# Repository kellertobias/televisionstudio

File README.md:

# Tobisk Television Studio Control Panel (ToskTVStudio)

This Project contains all software and hardware sources necessary to control a setup consisting of:

- ATEM Television Studio HD Video Switcher
- Web Presenter/ Hyperdeck (Work in Progress)
- OBS for graphics optionally streaming/recording
- Website based text generator for OBS
- MOTU828es based Audio Mixing (Work in Progress)
- LoRa Based Camera Tallys and Python based Tally base

The main part of this project is a nodejs based application that provides the control of the infrastructure via macros and all required additional services.

This System contains of these services:
- Main Control Desk Software
- Server to send Tally Signals (might run on the same raspberry pi as the control desk)
- Server to communicate with the hardware of the control desk
- Web based Textgenerator for OBS (or any other web browser)

as well as the firmware and schematics for these hardware components:
- LoRa Based Tally Sender and Receiver
- Desk Hardware Buttons, faders and encoders

## Control desk Software

The main part of this software is the control desk software which is capable of controlling ATEM switchers and OBS (Hyperdeck and Web Presenter Support is work in progress). This software is meant to run on a raspberry PI and provides the user interface via a website. there is also a serial interface to an arduino based keyboard interface (split up in a separate server for easier developing).

## Control desk Hardware

The main part of this software is the control desk software which is capable of controlling ATEM switchers and OBS (Hyperdeck and Web Presenter Support is work in progress). This software is meant to run on a raspberry PI and provides the user interface via a website. there is also a serial interface to an arduino based keyboard interface (split up in a separate server for easier developing).

## Tally System

The tally system is based on LoRa communications.
There is a server that is meant to run on the same raspberry pi as the control desk software. The control desk software sends to the LoRa server which channel is on program and which is on preview. This happens over a simple REST api.
However if you want to use the tally system without the control desk software, you can do so, but need to write this part your own. there are multiple libraries providing this.

The tally system consists out of:

- Tally Server: `/services/tally-lora-server`
- Tally Client Firmware & Hardware: `/services/tally-lora-client`

More information on this is in the README.md of that subproject: 

## Text-Generator

The last part of this software is a textgenerator. It is meant to be embedded as a webpage in OBS or as Fullscreen Browser Screen on a second raspberry pi and connected to the ATEM.

The textgenerator supports countdowns, scrolling texts and lower thirds

# Development and Operations

The software is written in Typescript and requires `node` and `npm` to be installed. You can then use `npm`'s scripts to execute development scripts.  

-   `npm i -D` for installing all the dependencies
-   `npm run dev` - Start Development Environment. Client and server are in watch mode with source maps, opens [http://localhost:3000](http://localhost:3000)

### Deploying

-   `npm run build` - `dist` folder will include all the needed files, both client (Bundle) and server.
-   `npm start` - Just runs `node ./dist/server/server.js`
-   `npm start:prod` - sets `NODE_ENV` to `production` and then runs `node ./dist/server/server.js`. (Bypassing webpack proxy)

### Technology Stack

Backend:

- `node.js` as runtime
- `typescript` as programming language
- `express` for APIs

Frontend:

- `webpack 5` for bundling
- `react` as UI Framework
- `storybook` for developing components
- `axios` for contacting the REST APIs

# Todo-List/ Roadmap

- [ ] get rid of meteor and move to a more modern build stack
- [ ] rewrite Web UI to be Typescript
- [ ] re-send tally commands multiple times
- [ ] Add Web Presenter Support (Start/Stop Stream, Show Stream Status, Set Stream Target configured in the showfile)
- [ ] Add Support for Audio Level Monitoring and Audio Control
- [ ] Add a second web interface for configuring the software, e.g. over an iPad or Laptop
- [ ] allow in-software macro editing and showfile configuration

# License

This software might only be used for non-commercial purposes, this means, you may not sell it or anything that builds upon it. You may however use your own products based on this software for commercial purposes.

Permission is hereby granted, free of charge, to any person obtaining a copy of this software and associated documentation files (the "Software"), to deal in the Software with the abovegiven restrictions, including with the abovegiven limitations the rights to use, copy, modify, merge, publish, distribute, of the Software, and to permit persons to whom the Software is furnished to do so, subject to the following conditions:

The above copyright notice and this permission notice shall be included in all copies or substantial portions of the Software.

THE SOFTWARE IS PROVIDED "AS IS", WITHOUT WARRANTY OF ANY KIND, EXPRESS OR IMPLIED, INCLUDING BUT NOT LIMITED TO THE WARRANTIES OF MERCHANTABILITY, FITNESS FOR A PARTICULAR PURPOSE AND NONINFRINGEMENT. IN NO EVENT SHALL THE AUTHORS OR COPYRIGHT HOLDERS BE LIABLE FOR ANY CLAIM, DAMAGES OR OTHER LIABILITY, WHETHER IN AN ACTION OF CONTRACT, TORT OR OTHERWISE, ARISING FROM, OUT OF OR IN CONNECTION WITH THE SOFTWARE OR THE USE OR OTHER DEALINGS IN THE SOFTWARE.

## References to packages and content this work is based on
- Boilerplate: https://github.com/gilamran/fullstack-typescript.git

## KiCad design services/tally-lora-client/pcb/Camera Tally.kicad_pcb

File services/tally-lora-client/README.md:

# Lora Tally Node

This part of the Project is a little Device (and the software for it), that you can stick onto the camera
and Lights up if the camera is on Program or Preview.

This part consists of the `lora-node.ino`, the arduino sourcecode for the Wemos D1, a little Python Script for the
Raspberry Pi to test the nodes and of the schematics and board layout.

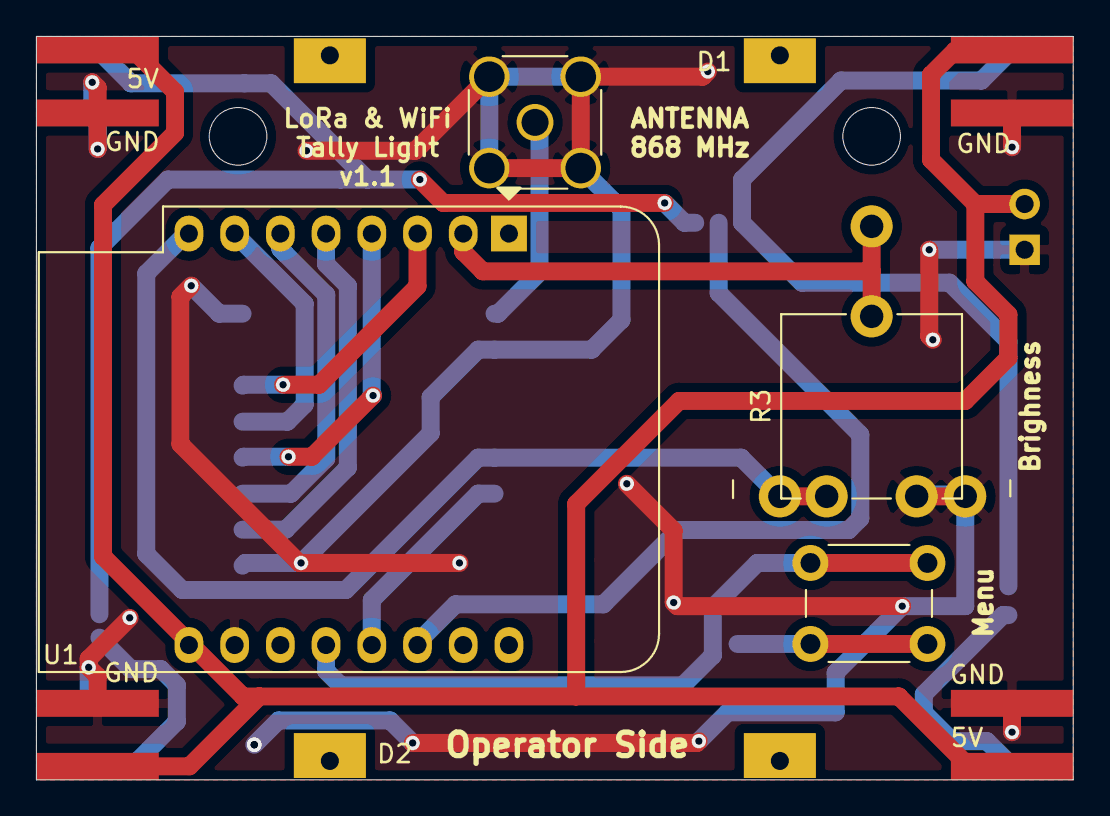
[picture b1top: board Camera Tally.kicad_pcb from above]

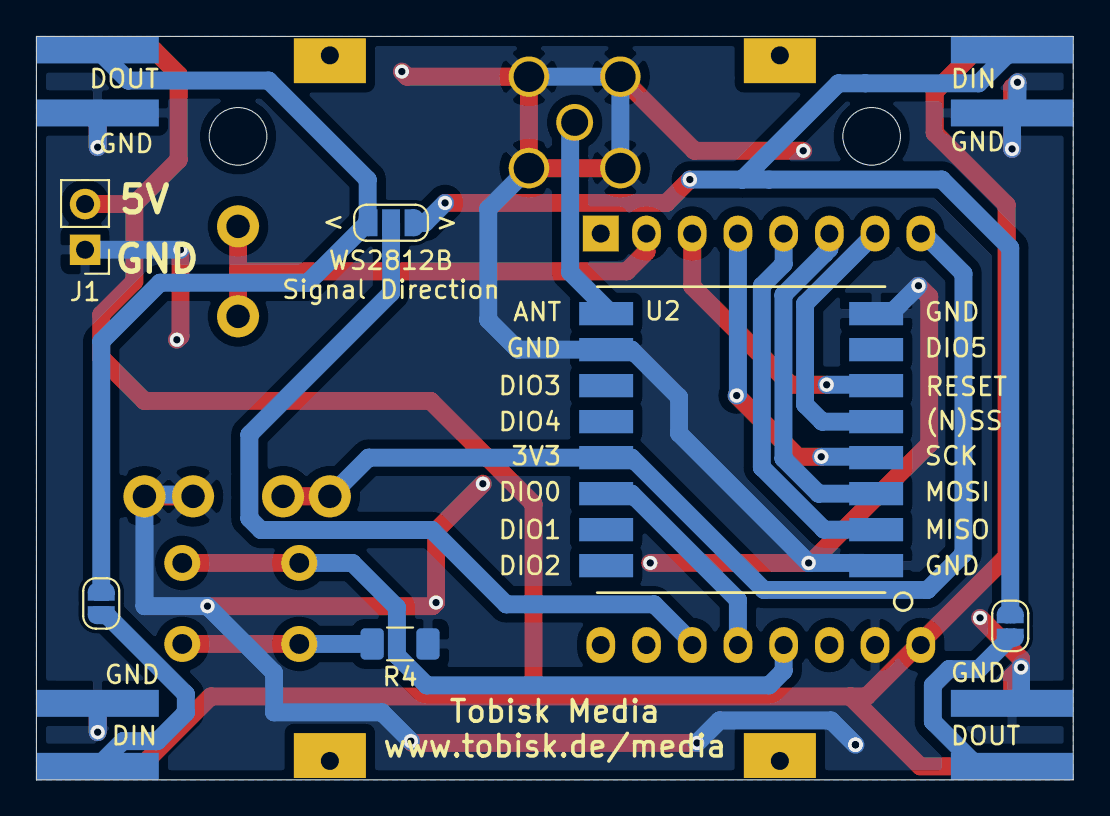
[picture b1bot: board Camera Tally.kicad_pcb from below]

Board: 2 copper layers, 57.6 x 41.3 mm, 14 parts (6 on the bottom side), 18 nets.

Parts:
AE2: Antenna_Shield; SMA_Wurth_60312002114503_Vertical
D1, D2: WS2812B; WS2812B_8x_5cm
H1, H2: MountingHole; MountingHole_3.2mm_M3
J1: Screw_Terminal_01x02; PinHeader_1x02_P2.54mm_Vertical
JP1, JP3: Jumper; SolderJumper-2_P1.3mm_Open_RoundedPad1.0x1.5mm
JP2: Jumper_NC_Dual; SolderJumper-3_P1.3mm_Open_RoundedPad1.0x1.5mm
R3: POT; Potentiometer_ACP_CA9-V10_Vertical
R4: R; R_1206_3216Metric_Pad1.30x1.75mm_HandSolder
SW1: SW_Push; SW_PUSH_6mm_H7.3mm
U1: WeMos_D1_mini; WEMOS_D1_mini_light
U2: RFM95W-868S2; RFM9X-SMD

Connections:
+3V3: R3.3, U1.8, U2.13
+5V: D1.1, D2.1, J1.2, U1.9
/ANT: AE2.1, U2.9
/MISO: U1.5, U2.2
/MOSI: U1.6, U2.3
/POT: R3.2, U1.2
/RFM_INT: U1.13, U2.14
/RFM_RES: U1.3, U2.6
/SCK: U1.4, U2.4
/SS: U1.7, U2.5
/SW1: SW1.1, U1.12
/WS2812B: JP2.2, U1.14
GND: AE2.2, D1.3, D2.3, J1.1, R3.1, R4.1, U1.10, U2.1, U2.8, U2.10
unnamed: D1.2, JP2.3, JP3.1
unnamed: D1.4, JP1.1, JP2.1
unnamed: D2.2, JP1.2
unnamed: D2.4, JP3.2
unnamed: R4.2, SW1.2

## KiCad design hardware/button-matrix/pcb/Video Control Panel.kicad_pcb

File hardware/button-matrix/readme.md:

# Control-Panel Button Matrix

The Control Panel consists of two Button Matrix Boards, connected via USB to a Raspberry PI as well as a Touchscreen and some miscalaneous electronics such as fans and a power supply.

The Button Matrix has at most 5 rows of 9 buttons each and can be cut so that it is 5x8. Each button has a WS2812b LED assigned to it.

The buttons and LEDs are numbered from the top left, row by row.

This means that the top left button has the number 11 (first row, first button), the last button of this row has the number 19.
The first button in the last row has the number 51, the last one 59. In the communication protocol, the ws2812b LEDs are also addressed by the button number.

The buttons might be populated or not, depending on the configuration required for the use case. If the button is not populated, the LED usually is also not populated, however the external addressing stays the same (meaning there is some calculation required.)

There are also some additional user inputs on the PCB, namely a push encoder and a linear slider.

The total addressing in the protocol is the following (the values are the range of values of the second byte, the value byte):

- 0 - System Messages (0 = startup, 255 = unit/connection will shutdown)
- 1 - LED Brightness Bright (0-255 for dark to bright)
- 2 - LED Brightness Dark (0-255 for dark to bright)
- 9 - Encoder Turn (1 = Left Turn, 2 = Right Turn, Encoder Push is the same contact as button 58)
- 10 - Linear Slider (0-255 for 0v to 5V)
- 11 - Row 1 Button/LED 1 (for button: 0 = not pressed, 1 = pressed, for LED: one byte containing two sets of colors)
- ...
- 19 - Row 1 Button/LED 9 (...)
- ...
- 59 - Row 5 Button/LED 9 (...)

# Communication Protocol

The Communication Protocol uses UART and the first Byte in a Message defines the entity as described above.
When the Device starts up, it sends a Zero-Byte. Messages where the first byte is zero are system messages.

## Event-Messages from PCB to Master (Buttons and Faders)

when sending input messages, such as button presses or fader value changes, the first byte is the address, the second one is the state, such as 0 or 1 for a button (0 = not pressed, 1 = pressed) or 0-255 for a fader (where the range of the fader is mapped to 0-255).

The Encoder, if populated also can send messages. If it turns left, the message is 1 (per click), for right it is 2.
The push of the encoder is the same as button number 58

## Event-Messages from Master to PCB (LED status change, Brightness)

The master might also send messages to the controller, containing LED states.
The value of the led states is as follows:

ON R | ON G | ON B | BLINK R | BLINK G | BLINK B | BLINK FAST=1/SLOW=0 | DIM BRIGHT=1/DARK=0

the led needs to change color 4 times a second, if blink=fast, two times a second if blink=slow. It changes from the color from he first three bits to the one of the last three bits.
The Color is always mapped from bit to byte => 0 = 0x00 and 1 = 0x01 \* global brightness

Thus the brightness is determined by the globally set brightess, which is set by a message on address 1 (or 2 if the last bit of the led value is set to 0 and thus its meant to be a dark glow)

# Connections

For the connection diagram see

Note that the Diodes are Placed in reverse order to the Circuit.
So the Rows are the Output, which are set to high and the columns are the inputs, which can be read (High = Pressed, Low = Open)

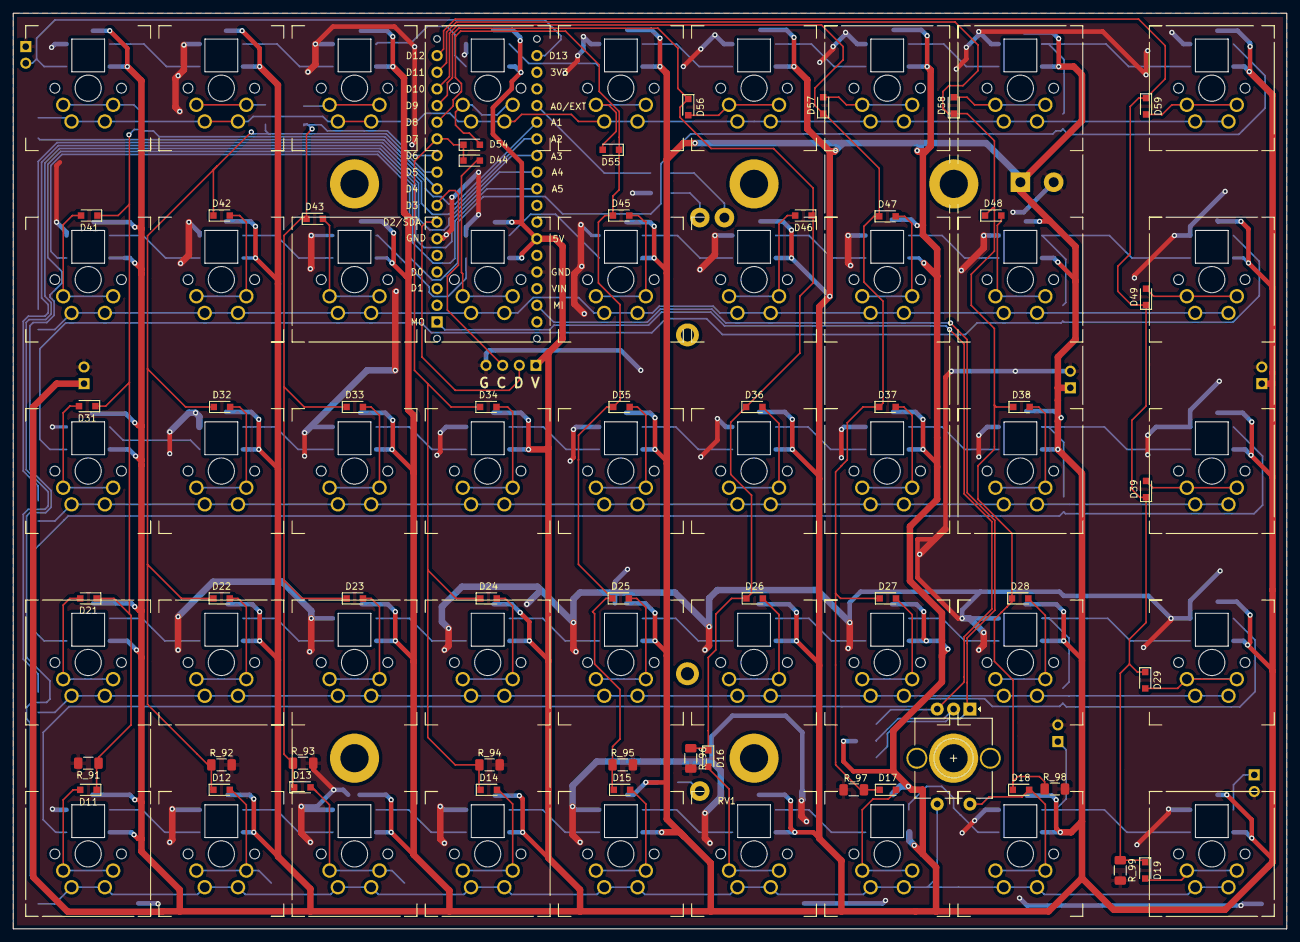
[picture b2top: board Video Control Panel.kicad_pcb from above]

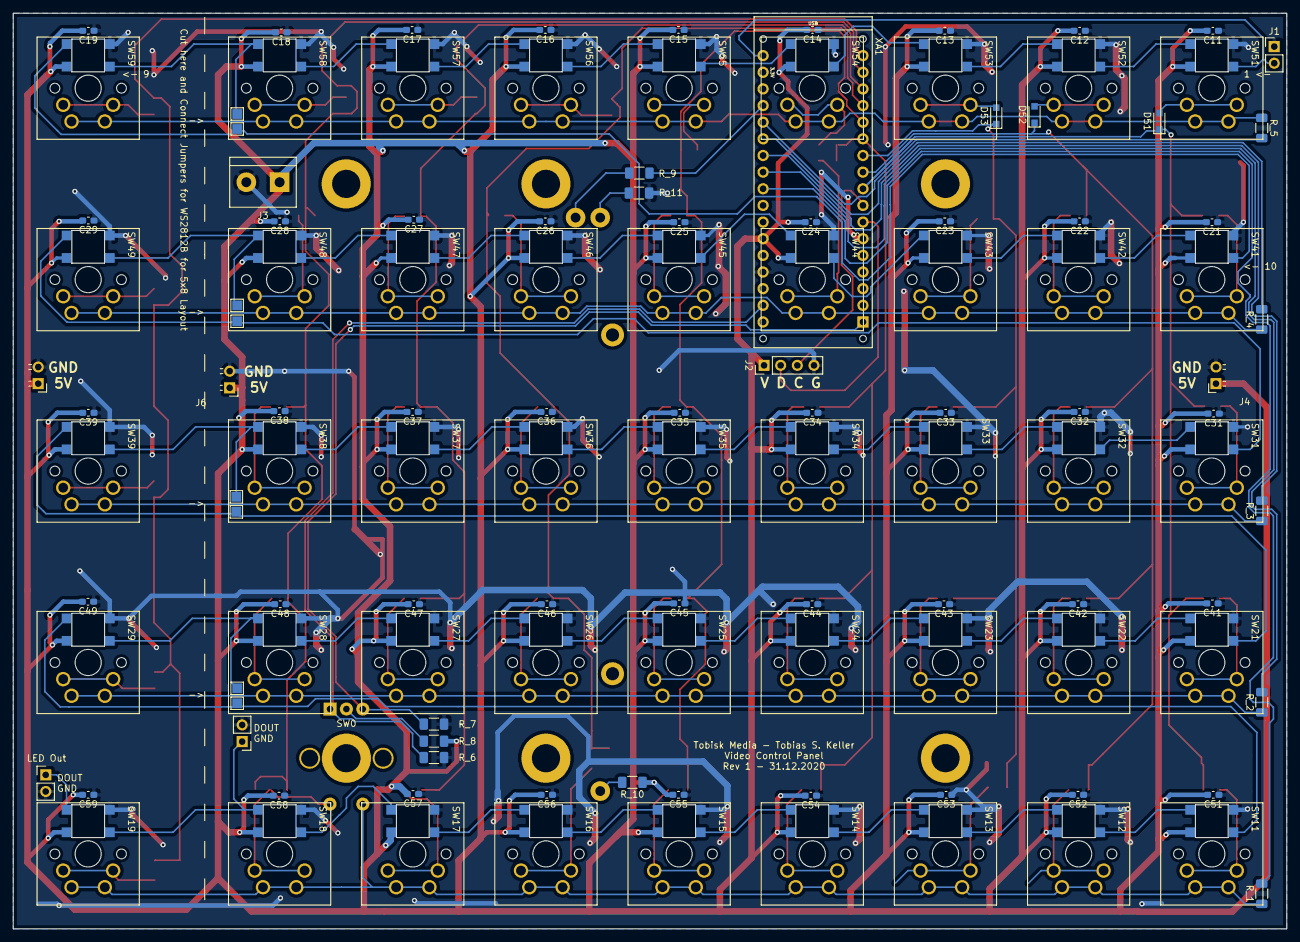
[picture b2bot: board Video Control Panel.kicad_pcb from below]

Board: 2 copper layers, 194.3 x 139.7 mm, 180 parts (121 on the bottom side), 121 nets.

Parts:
C11, C12, C13, C14, C15, C16, C17, C18, C19, C21, C22, C23, C24, C25, C26, C27, C28, C29, C31, C32, C33, C34, C35, C36, C37, C38, C39, C41, C42, C43, C44, C45, C46, C47, C48, C49, C51, C52, C53, C54, C55, C56, C57, C58, C59: cap_np; C_0603_1608Metric_Pad1.08x0.95mm_HandSolder
D11, D12, D13, D14, D15, D16, D17, D18, D19, D21, D22, D23, D24, D25, D26, D27, D28, D29, D31, D32, D33, D34, D35, D36, D37, D38, D39, D41, D42, D43, D44, D45, D46, D47, D48, D49, D51, D52, D53, D54, D55, D56, D57, D58, D59: DIODE; D_SOD-323_HandSoldering
H1, H2, H3, H4, H5, H6: MountingHole; MountingHole_4.3mm_M4_DIN965_Pad
J1, J7, J8: HEADER_2; PinHeader_1x02_P2.54mm_Vertical
J2: HEADER_4; PinHeader_1x04_P2.54mm_Vertical
J3: HEADER_2; TerminalBlock_bornier-2_P5.08mm
J4: HEADER_2; PinSocket_1x02_P2.54mm_Horizontal
J5, J6: HEADER_2; PinHeader_1x02_P2.54mm_Horizontal
J9, J10, J12, J13, J15, J16, J18, J19: HEADER_1; TestPoint_Pad_1.5x1.5mm
RV1: R_POT; ALPS_RS60N
R_1, R_2, R_3, R_4, R_5, R_6, R_7, R_8, R_9, R_10, R_11, R_91, R_92, R_93, R_94, R_95, R_96, R_97, R_98, R_99: R; R_1206_3216Metric_Pad1.30x1.75mm_HandSolder
SW0: Rotary_Encoder_Switch; RotaryEncoder_Alps_EC11E-Switch_Vertical_H20mm_CircularMoun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
SW11, SW12, SW13, SW14, SW15, SW16, SW17, SW18, SW19, SW21, SW22, SW23, SW24, SW25, SW26, SW27, SW28, SW29, SW31, SW32, SW33, SW34, SW35, SW36, SW37, SW38, SW39, SW41, SW42, SW43, SW44, SW45, SW46, SW47, SW48, SW49, SW51, SW52, SW53, SW54, SW55, SW56, SW57, SW58, SW59: SW_WS2812B; Cherry_MX_SK6812_BS
XA1: Arduino_Micro_Socket

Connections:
5V: C11.2, C12.2, C13.2, C14.2, C15.2, C16.2, C17.2, C18.2, C19.2, C21.2, C22.2, C23.2, C24.2, C25.2, C26.2, C27.2, C28.2, C29.2, C31.2, C32.2, C33.2, C34.2, C35.2, C36.2, C37.2, C38.2, C39.2, C41.2, C42.2, C43.2, C44.2, C45.2, C46.2, C47.2, C48.2, C49.2, C51.2, C52.2, C53.2, C54.2, C55.2, C56.2, C57.2, C58.2, C59.2, J2.1, J3.1, J4.1, J5.1, J6.1, R_8.2, R_10.1, SW11.3, SW12.3, SW13.3, SW14.3, SW15.3, SW16.3, SW17.3, SW18.3, SW19.3, SW21.3, SW22.3, SW23.3, SW24.3, SW25.3, SW26.3, SW27.3, SW28.3, SW29.3, SW31.3, SW32.3, SW33.3, SW34.3, SW35.3, SW36.3, SW37.3, SW38.3, SW39.3, SW41.3, SW42.3, SW43.3, SW44.3, SW45.3, SW46.3, SW47.3, SW48.3, SW49.3, SW51.3, SW52.3, SW53.3, SW54.3, SW55.3, SW56.3, SW57.3, SW58.3, SW59.3, XA1.5V
COL1: D11.1, D21.1, D31.1, D41.1, D51.1, R_91.1, XA1.D4
COL2: D12.1, D22.1, D32.1, D42.1, D52.1, R_92.1, XA1.D5
COL3: D13.1, D23.1, D33.1, D43.1, D53.1, R_93.1, XA1.D6
COL4: D14.1, D24.1, D34.1, D44.1, D54.1, R_94.1, XA1.D7
COL5: D15.1, D25.1, D35.1, D45.1, D55.1, R_95.1, XA1.D8
COL6: D16.1, D26.1, D36.1, D46.1, D56.1, R_96.1, XA1.D9
COL7: D17.1, D27.1, D37.1, D47.1, D57.1, R_97.1, XA1.D10
COL8: D18.1, D28.1, D38.1, D48.1, D58.1, R_98.1, XA1.D11
COL9: D19.1, D29.1, D39.1, D49.1, D59.1, R_99.1, XA1.D12
ENC_A: R_6.1, SW0.A, XA1.MISO
ENC_B: R_7.1, SW0.B, XA1.MOSI
FADE: R_9.2, XA1.A0
GND: C11.1, C12.1, C13.1, C14.1, C15.1, C16.1, C17.1, C18.1, C19.1, C21.1, C22.1, C23.1, C24.1, C25.1, C26.1, C27.1, C28.1, C29.1, C31.1, C32.1, C33.1, C34.1, C35.1, C36.1, C37.1, C38.1, C39.1, C41.1, C42.1, C43.1, C44.1, C45.1, C46.1, C47.1, C48.1, C49.1, C51.1, C52.1, C53.1, C54.1, C55.1, C56.1, C57.1, C58.1, C59.1, J1.1, J2.4, J3.2, J4.2, J5.2, J6.2, J7.2, J8.2, R_6.2, R_7.2, R_11.2, R_91.2, R_92.2, R_93.2, R_94.2, R_95.2, R_96.2, R_97.2, R_98.2, R_99.2, SW11.6, SW12.6, SW13.6, SW14.6, SW15.6, SW16.6, SW17.6, SW18.6, SW19.6, SW21.6, SW22.6, SW23.6, SW24.6, SW25.6, SW26.6, SW27.6, SW28.6, SW29.6, SW31.6, SW32.6, SW33.6, SW34.6, SW35.6, SW36.6, SW37.6, SW38.6, SW39.6, SW41.6, SW42.6, SW43.6, SW44.6, SW45.6, SW46.6, SW47.6, SW48.6, SW49.6, SW51.6, SW52.6, SW53.6, SW54.6, SW55.6, SW56.6, SW57.6, SW58.6, SW59.6, XA1.GND1, XA1.GND2
unnamed: D11.2, SW11.1
unnamed: D12.2, SW12.1
unnamed: D13.2, SW13.1
unnamed: D14.2, SW14.1
unnamed: D15.2, SW15.1
unnamed: D16.2, SW16.1
unnamed: D17.2, SW17.1
unnamed: D18.2, SW0.S2, SW18.1
unnamed: D19.2, SW19.1
unnamed: D21.2, SW21.1
unnamed: D22.2, SW22.1
unnamed: D23.2, SW23.1
unnamed: D24.2, SW24.1
unnamed: D25.2, SW25.1
unnamed: D26.2, SW26.1
unnamed: D27.2, SW27.1
unnamed: D28.2, SW28.1
unnamed: D29.2, SW29.1
unnamed: D31.2, SW31.1
unnamed: D32.2, SW32.1
unnamed: D33.2, SW33.1
unnamed: D34.2, SW34.1
unnamed: D35.2, SW35.1
unnamed: D36.2, SW36.1
unnamed: D37.2, SW37.1
unnamed: D38.2, SW38.1
unnamed: D39.2, SW39.1
unnamed: D41.2, SW41.1
unnamed: D42.2, SW42.1
unnamed: D43.2, SW43.1
unnamed: D44.2, SW44.1
unnamed: D45.2, SW45.1
unnamed: D46.2, SW46.1
unnamed: D47.2, SW47.1
unnamed: D48.2, SW48.1
unnamed: D49.2, SW49.1
unnamed: D51.2, SW51.1
unnamed: D52.2, SW52.1
unnamed: D53.2, SW53.1
unnamed: D54.2, SW54.1
unnamed: D55.2, SW55.1
unnamed: D56.2, SW56.1
unnamed: D57.2, SW57.1
unnamed: D58.2, SW58.1
unnamed: D59.2, SW59.1
unnamed: J7.1, SW18.4, SW19.5
unnamed: J8.1, SW19.4
unnamed: J9.1, SW28.4, SW29.5
unnamed: J10.1, SW11.5, SW29.4
unnamed: J12.1, SW21.5, SW39.4
unnamed: J13.1, SW38.4, SW39.5
unnamed: J15.1, SW48.4, SW49.5
unnamed: J16.1, SW31.5, SW49.4
unnamed: J18.1, SW58.4, SW59.5
unnamed: J19.1, SW41.5, SW59.4
unnamed: RV1.1, R_11.1
unnamed: RV1.2, R_9.1
unnamed: RV1.3, R_10.2
unnamed: R_1.2, XA1.A5
unnamed: R_2.2, XA1.A4
unnamed: R_3.2, XA1.A3
unnamed: R_4.2, XA1.A2
unnamed: R_5.2, XA1.A1
unnamed: R_8.1, SW0.C
unnamed: SW11.4, SW12.5
unnamed: SW12.4, SW13.5
unnamed: SW13.4, SW14.5
unnamed: SW14.4, SW15.5
unnamed: SW15.4, SW16.5
unnamed: SW16.4, SW17.5
unnamed: SW17.4, SW18.5
unnamed: SW21.4, SW22.5
unnamed: SW22.4, SW23.5
unnamed: SW23.4, SW24.5
unnamed: SW24.4, SW25.5
unnamed: SW25.4, SW26.5
unnamed: SW26.4, SW27.5
unnamed: SW27.4, SW28.5
unnamed: SW31.4, SW32.5
unnamed: SW32.4, SW33.5
unnamed: SW33.4, SW34.5
unnamed: SW34.4, SW35.5
unnamed: SW35.4, SW36.5
unnamed: SW36.4, SW37.5
unnamed: SW37.4, SW38.5
unnamed: SW41.4, SW42.5
unnamed: SW42.4, SW43.5
unnamed: SW43.4, SW44.5
unnamed: SW44.4, SW45.5
unnamed: SW45.4, SW46.5
unnamed: SW46.4, SW47.5
unnamed: SW47.4, SW48.5
unnamed: SW51.4, SW52.5
unnamed: SW52.4, SW53.5
unnamed: SW53.4, SW54.5
unnamed: SW54.4, SW55.5
unnamed: SW55.4, SW56.5
unnamed: SW56.4, SW57.5
unnamed: SW57.4, SW58.5
ROW1: R_1.1, SW0.S1, SW11.2, SW12.2, SW13.2, SW14.2, SW15.2, SW16.2, SW17.2, SW18.2, SW19.2
ROW2: R_2.1, SW21.2, SW22.2, SW23.2, SW24.2, SW25.2, SW26.2, SW27.2, SW28.2, SW29.2
ROW3: R_3.1, SW31.2, SW32.2, SW33.2, SW34.2, SW35.2, SW36.2, SW37.2, SW38.2, SW39.2
ROW4: R_4.1, SW41.2, SW42.2, SW43.2, SW44.2, SW45.2, SW46.2, SW47.2, SW48.2, SW49.2
ROW5: R_5.1, SW51.2, SW52.2, SW53.2, SW54.2, SW55.2, SW56.2, SW57.2, SW58.2, SW59.2
SCL: J2.3, XA1.D3
SDA: J2.2, XA1.D2
WS2812: J1.2, SW51.5, XA1.D13

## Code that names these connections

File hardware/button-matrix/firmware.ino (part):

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#define SERIAL_FOOTER_A 0b11111111
#define SERIAL_FOOTER_B 0b00000000

#define ROW1 23 //A5
#define ROW2 22 //A4
#define ROW3 21 //A3
#define ROW4 20 //A2
#define ROW5 19 //A1

#define COL1 4
#define COL2 5
#define COL3 6
#define COL4 7
#define COL5 8
#define COL6 9
#define COL7 10
#define COL8 11
#define COL9 12

#define ENC_A 14
#define ENC_B 16

// Free Pins: SCK(15), CS(17), TX(1), RX(0)

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        pinMode(cols[i], INPUT_PULLUP);
    }

    pinMode(ENC_A, INPUT);
    pinMode(ENC_B, INPUT);

    //Setup Arrays
    for (int i = 0; i < NUMROW * NUMCOL; i++)
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
void readEncoder()
{
    encoderPinACur = digitalRead(ENC_A);

    if (
        (encoderPinALast == LOW) &&
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
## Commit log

2021-06-05 Initial Release Commit
2021-06-05 add images
2021-06-05 image width?
2021-06-05 Remove image widths again -_-
2021-06-05 change image sizes
2022-01-18 add new firmware
2022-01-18 Left/Right => Single Serial Driver
2022-01-18 Fix Compiler Issues
2022-01-18 Update Package JSON
2022-01-18 Config for single serial keyboard
2022-01-21 Working Button Board Firmware
2022-01-21 New Serial Firmware Protocol
2022-01-23 Move Serial Connection to separate application
2022-01-23 Startup Script
2022-01-23 Improve Keyboard Logging
2022-01-23 Live Version?
2022-01-24 Serial Proxy as own service
2022-01-24 Refactor to new codebase
2022-01-24 Update Versions
2022-01-24 Only Automatic Prettification
2022-01-24 Improve Code
2022-01-24 Finish refactor of modules
2022-01-24 Refactor all Prettier errors in server
2022-01-24 Finishing Touches for Server
2022-01-25 Preparation to move Client to TS
2022-01-25 Initial Client Code for TS
2022-01-26 Client API Connection and Combined Websocket Server
2022-01-26 Move WS to Express WS
2022-01-26 Further Client Refactoring (Styles)
2022-01-26 Add Widgets
2022-01-27 Migrated all Windows to tsx (Modals still missing)
2022-01-27 Prepare Macros
2022-01-31 Modal Functionality
2022-01-31 Load File Modal
2022-01-31 Typing of Showfile Loading
2022-02-13 Improved Status Display
2022-02-13 Show Loading in new UI
2022-02-13 Correct button colors
2022-02-13 Saving Show Start in new UI
2022-02-13 Fix Macro Selection Offset
2022-02-13 video norm loading instead of ???@NaN
2022-02-13 Connection Errors
2022-02-13 Fixed bug in Loading Showfile
2022-02-13 Improve Status Sections for currently finishd services
2022-02-13 Send Tally Information in an interval
2022-04-20 Full Date for show start
2022-04-20 Closing Banners
2022-04-20 Status Messages
2022-04-20 Dev Version of Keyboard Server
2022-04-20 Debug for Keyboard
2022-04-22 remove old deploy script
2022-04-22 Add new deployment script
2022-04-24 Keyboard Working
2022-11-23 Fix global variable undefined
2023-04-01 ADd new Kicad files
